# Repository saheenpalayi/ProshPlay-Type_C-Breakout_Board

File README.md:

# ProshPlay-Type_C-Breakout_Board

It's Hard to mill and solder Type C sockets in the Fab Prototyping PCBs So decided to make a breakout board to clear this issue and the breakout board can be mass manufacturable in less cost and can be assembled using a pick and place machine at the fab 

PCB made by Fab academy 2023 student [Sreyas George](https://fabacademy.org/2023/labs/kochi/students/sreyas-george/)

Downloads
 - [Kicad Library](https://github.com/saheenpalayi/ProshPlay-Type_C-Breakout_Board/raw/main/Library%20Files/Kicad/ProshPlay-Type_C-Breakout_Board.zip)
 - [Gerber File](https://github.com/saheenpalayi/ProshPlay-Type_C-Breakout_Board/raw/main/Gerber%20Files/V1/type-C-Breakout.zip)

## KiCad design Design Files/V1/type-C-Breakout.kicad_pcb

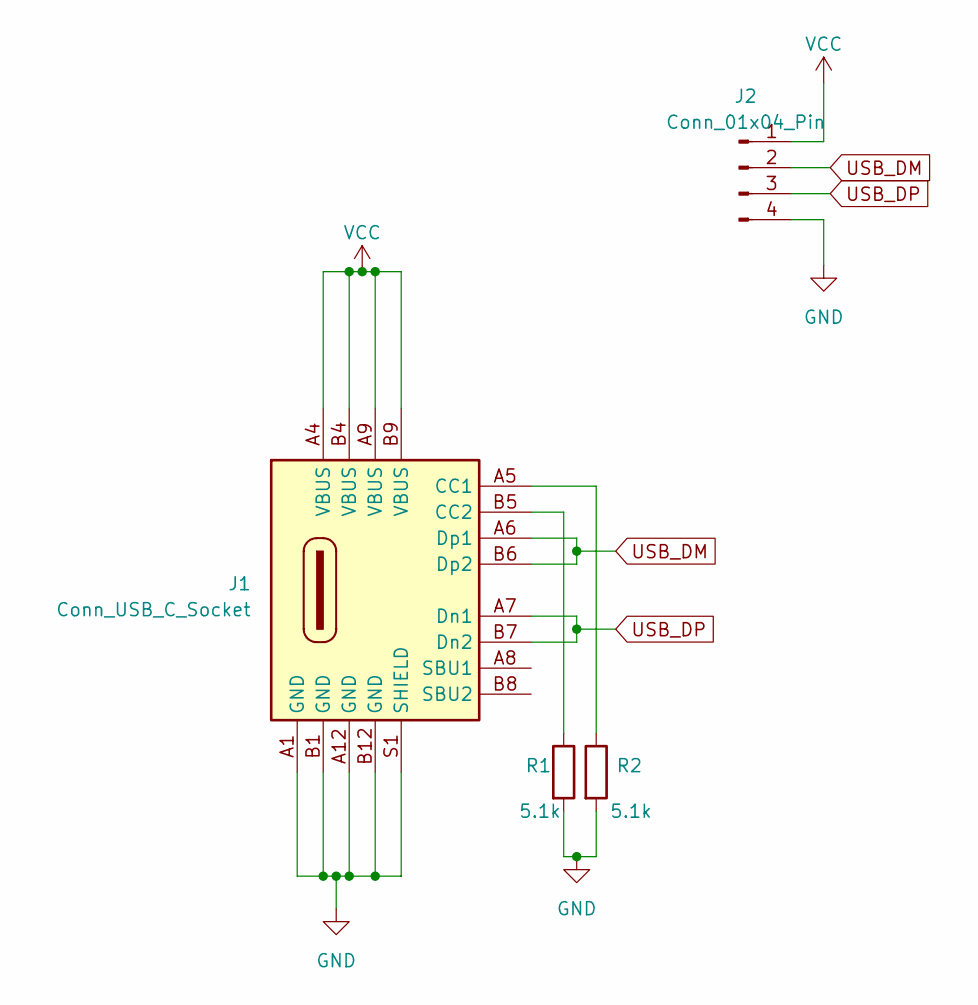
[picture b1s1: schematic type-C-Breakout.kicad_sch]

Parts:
J1: Conn_USB_C_Socket; Conn_USB_C_Socket_Molex_2171790001
J2: Conn_01x04_Pin; PinHeader_1x04_P2.54mm_PCB-Edge
R1, R2: 5.1k; R_0805_2012Metric_Pad1.20x1.40mm_HandSolder

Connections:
GND: J1.A1 (GND), J1.A12 (GND), J1.B1 (GND), J1.B12 (GND), J1.S1 (SHIELD), J2.4, R1.2, R2.2
unnamed: J1.A5 (CC1), R2.1
unnamed: J1.B5 (CC2), R1.1
USB_DM: J1.A6 (Dp1), J1.B6 (Dp2), J2.2
USB_DP: J1.A7 (Dn1), J1.B7 (Dn2), J2.3
VCC: J1.A4 (VBUS), J1.A9 (VBUS), J1.B4 (VBUS), J1.B9 (VBUS), J2.1

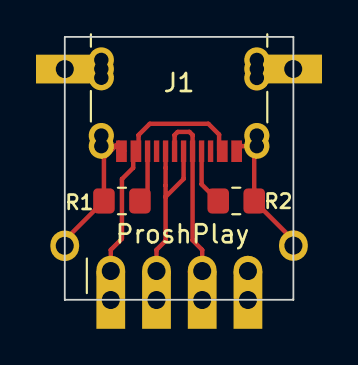
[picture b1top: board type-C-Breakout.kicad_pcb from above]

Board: 2 copper layers, 12.7 x 14.6 mm, 4 parts (0 on the bottom side), 6 nets.

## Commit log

2024-03-20 Files attached
2024-03-20 readme-update and kicad lib files
    added a zip file to kicad library files for easy downloaded
    and added images
2024-03-20 download link update and compressed images
